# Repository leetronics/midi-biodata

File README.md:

# MIDI Biodata Sonification system

This repository was originally a fork of https://github.com/electricityforprogress/MIDIsprout, but is now maintained seperately by 13-37.org electronics.

Here you find the hardware and enclosure design files for the MIDI Biodata Sonification Devices produced by 13-37.org electronics.

- enclosures: contains FreeCAD design and STL files for the enclosure
- firmware: 
  - MIDI_Psychogalv_328p_v021: unmodified firmware from electricityforprogress/MIDIsprout
  - MIDI_Psychogalv_328p_13-37.org_v2.0: firmware for MIDI Biodata Sonification Device by 13-37.org electronics
- kicad: hardware design as KiCAD project and Gerber files

The hardware design and firmware is based on the work of electricityforprogress and thus licensed under the MIT license.

The enclosure design is however licensed under CC0 (public domain), except for the logo which is under copyright of [DipthDesign](https://www.dipth.de). For private use, anyone is free to print the enclosure with logo and without permission.

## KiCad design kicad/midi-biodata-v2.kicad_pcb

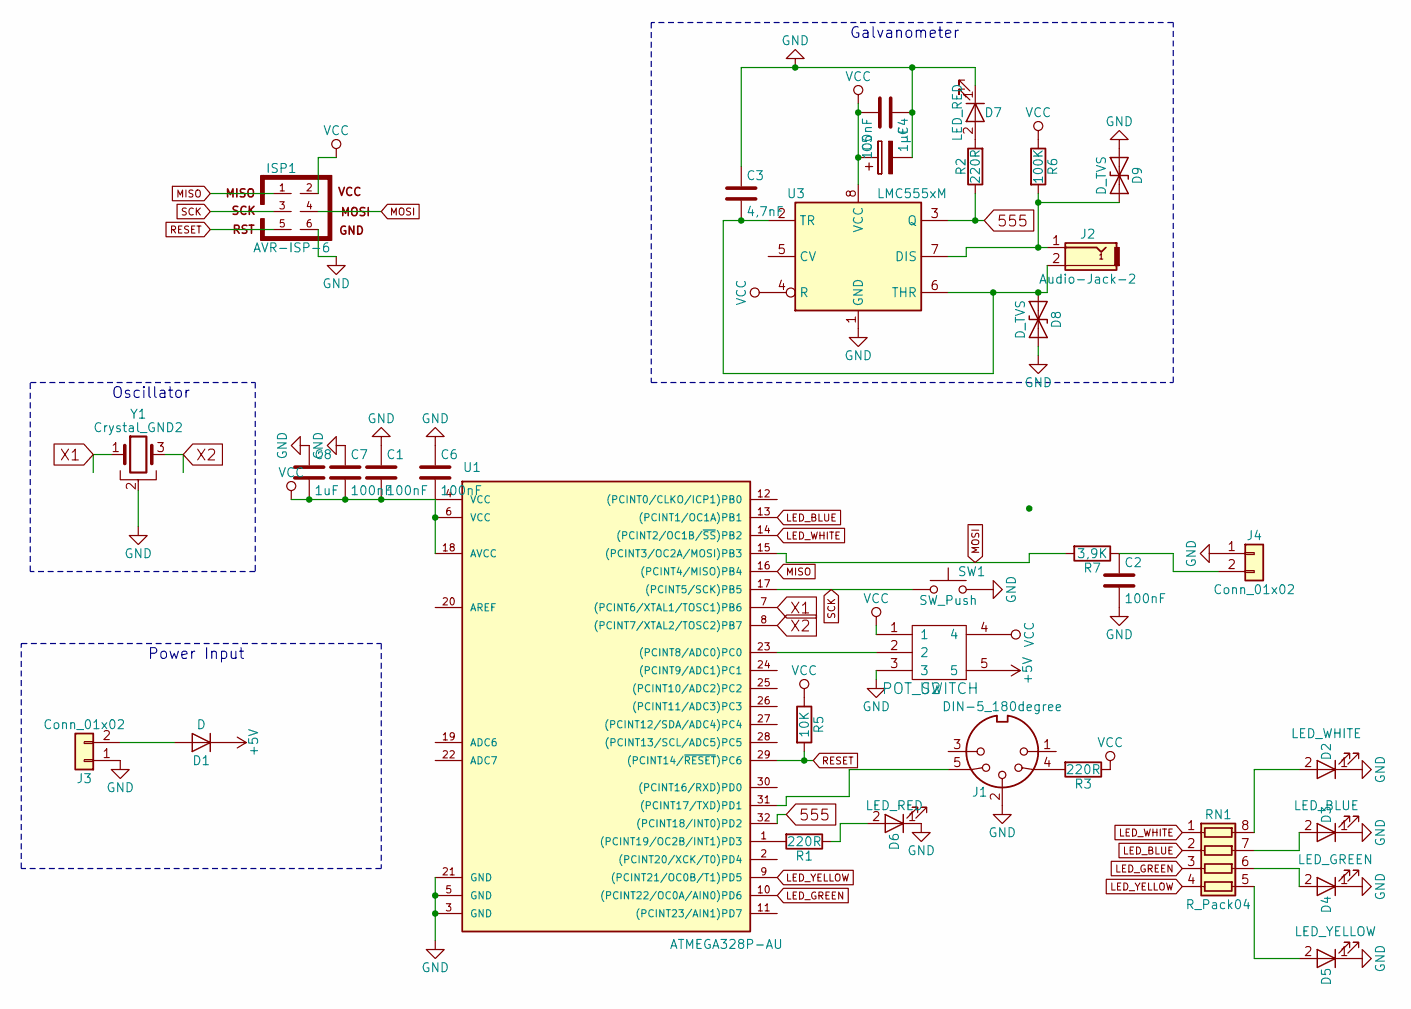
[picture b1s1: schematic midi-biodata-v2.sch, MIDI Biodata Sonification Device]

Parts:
C1, C2, C4: 100nF; C_1206
C3: 4,7nF; C_1206
C5: 1µF; CP_Radial_D5.0mm_P2.50mm
C6, C7: 100nF; C_0805
C8: 1uF; C_0805
D1: D; D_1206
D2: LED_WHITE; LED_1206_HandSoldering
D3: LED_BLUE; LED_1206_HandSoldering
D4: LED_GREEN; LED_1206_HandSoldering
D5: LED_YELLOW; LED_1206_HandSoldering
D6, D7: LED_RED; LED_1206_HandSoldering
D8, D9: D_TVS; D_0805
ISP1: AVR-ISP-6; Pin_Header_Straight_2x03_Pitch2.54mm
J1: DIN-5_180degree; DIN-5-MIDI-JACK
J2: Audio-Jack-2; mono-jack
J3, J4: Conn_01x02; Pin_Header_Straight_1x02_Pitch2.54mm
R1, R2, R3: 220R; R_1206
R5: 10K; R_0805
R6: 100K; R_1206
R7: 3,9K; R_1206
RN1: R_Pack04; R_Array_Concave_4x0603
SW1: SW_Push; SW_Tactile_SPST_Angled
U1: ATMEGA328P-AU; TQFP-32_7x7mm_Pitch0.8mm
U2: POT_SWITCH
U3: LMC555xM; DIP-8_W7.62mm
Y1: Crystal_GND2; murata-cstce

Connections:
555: R2.1, U1.32 ((PCINT18/INT0)PD2), U3.3 (Q)
+5V: D1.1 (K), U2.5
GND: C1.1, C2.2, C3.1, C4.1, C5.2, C6.1, C7.1, C8.1, D2.1 (K), D3.1 (K), D4.1 (K), D5.1 (K), D6.1 (K), D7.1 (K), D8.2 (A2), D9.1 (A1), ISP1.6, J1.2, J3.1, J4.1, SW1.2, U1.3 (GND), U1.5 (GND), U1.21 (GND), U2.3, U3.1 (GND), Y1.2
LED_BLUE: RN1.2 (R2.1), U1.13 ((PCINT1/OC1A)PB1)
LED_GREEN: RN1.3 (R3.1), U1.10 ((PCINT22/OC0A/AIN0)PD6)
LED_WHITE: RN1.1 (R1.1), U1.14 ((PCINT2/OC1B/~SS~)PB2)
LED_YELLOW: RN1.4 (R4.1), U1.9 ((PCINT21/OC0B/T1)PD5)
MISO: ISP1.1, U1.16 ((PCINT4/MISO)PB4)
MOSI: ISP1.4, R7.2, U1.15 ((PCINT3/OC2A/MOSI)PB3)
unnamed: C2.1, J4.2, R7.1
unnamed: C3.2, D8.1 (A1), J2.2, U3.2 (TR), U3.6 (THR)
unnamed: D1.2 (A), J3.2
unnamed: D2.2 (A), RN1.8 (R1.2)
unnamed: D3.2 (A), RN1.7 (R2.2)
unnamed: D4.2 (A), RN1.6 (R3.2)
unnamed: D5.2 (A), RN1.5 (R4.2)
unnamed: D6.2 (A), R1.1
unnamed: D7.2 (A), R2.2
unnamed: D9.2 (A2), J2.1, R6.2, U3.7 (DIS)
unnamed: J1.4, R3.2
unnamed: J1.5, U1.31 ((PCINT17/TXD)PD1)
unnamed: R1.2, U1.1 ((PCINT19/OC2B/INT1)PD3)
unnamed: U1.23 ((PCINT8/ADC0)PC0), U2.2
RESET: ISP1.5, R5.2, U1.29 ((PCINT14/~RESET~)PC6)
SCK: ISP1.3, SW1.1, U1.17 ((PCINT5/SCK)PB5)
VCC: C1.2, C4.2, C5.1, C6.2, C7.2, C8.2, ISP1.2, R3.1, R5.1, R6.1, U1.4 (VCC), U1.6 (VCC), U1.18 (AVCC), U2.1, U2.4, U3.4 (R), U3.8 (VCC)
X1: U1.7 ((PCINT6/XTAL1/TOSC1)PB6), Y1.1
X2: U1.8 ((PCINT7/XTAL2/TOSC2)PB7), Y1.3

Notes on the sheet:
Galvanometer
Oscillator
Power Input

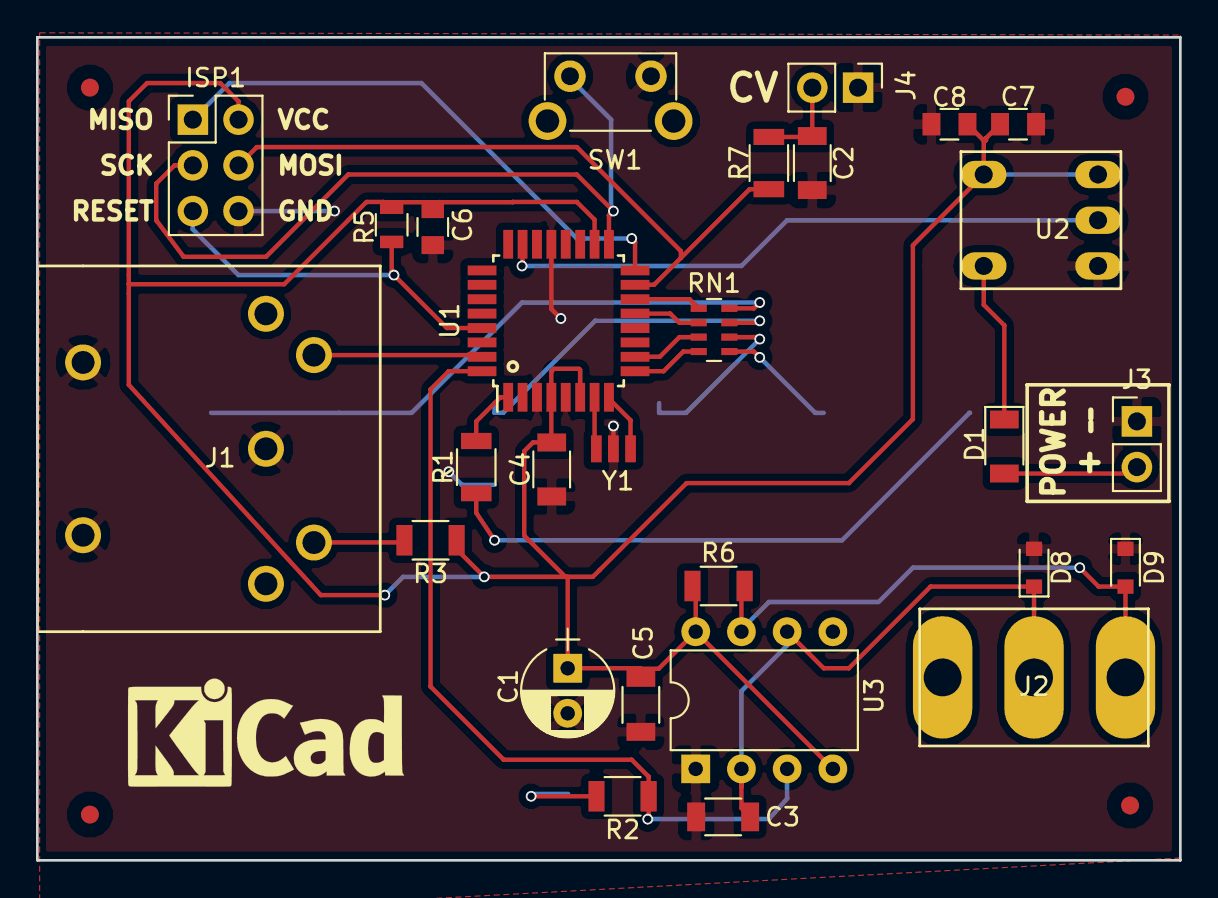
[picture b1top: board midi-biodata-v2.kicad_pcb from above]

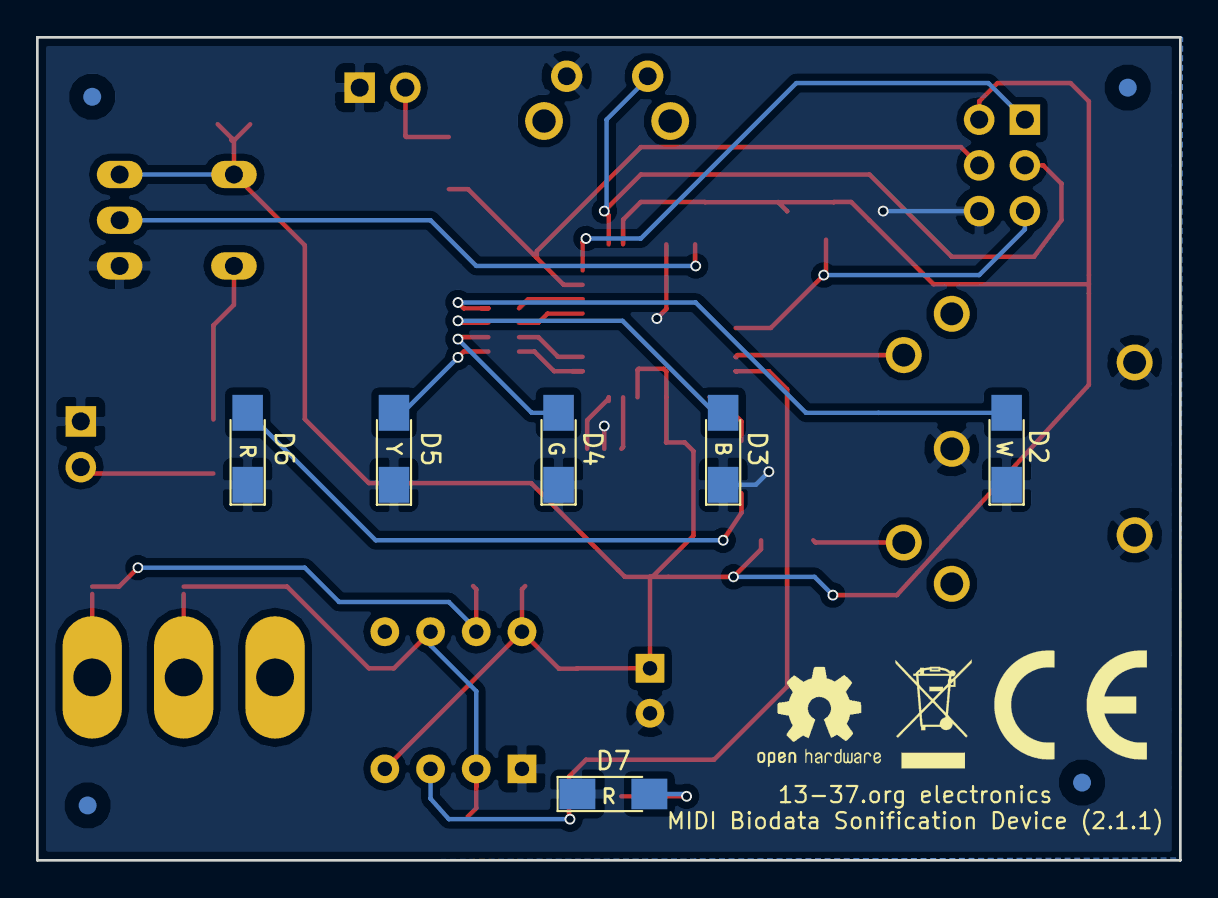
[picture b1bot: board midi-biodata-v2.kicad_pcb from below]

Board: 2 copper layers, 63.5 x 45.7 mm, 34 parts (6 on the bottom side), 28 nets.

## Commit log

2019-03-21 upload midi biodata source files
2019-03-21 upload v2.1
2019-03-22 updated enclosure design files
2019-03-22 increased button hole and flipped logo
2019-03-22 move button position
2019-03-22 add some clearance
2019-03-24 configure MIDI channel with visual feedback (binary encoded using 5 LEDs)
2019-04-19 increase hole diameter for MIDI connector
